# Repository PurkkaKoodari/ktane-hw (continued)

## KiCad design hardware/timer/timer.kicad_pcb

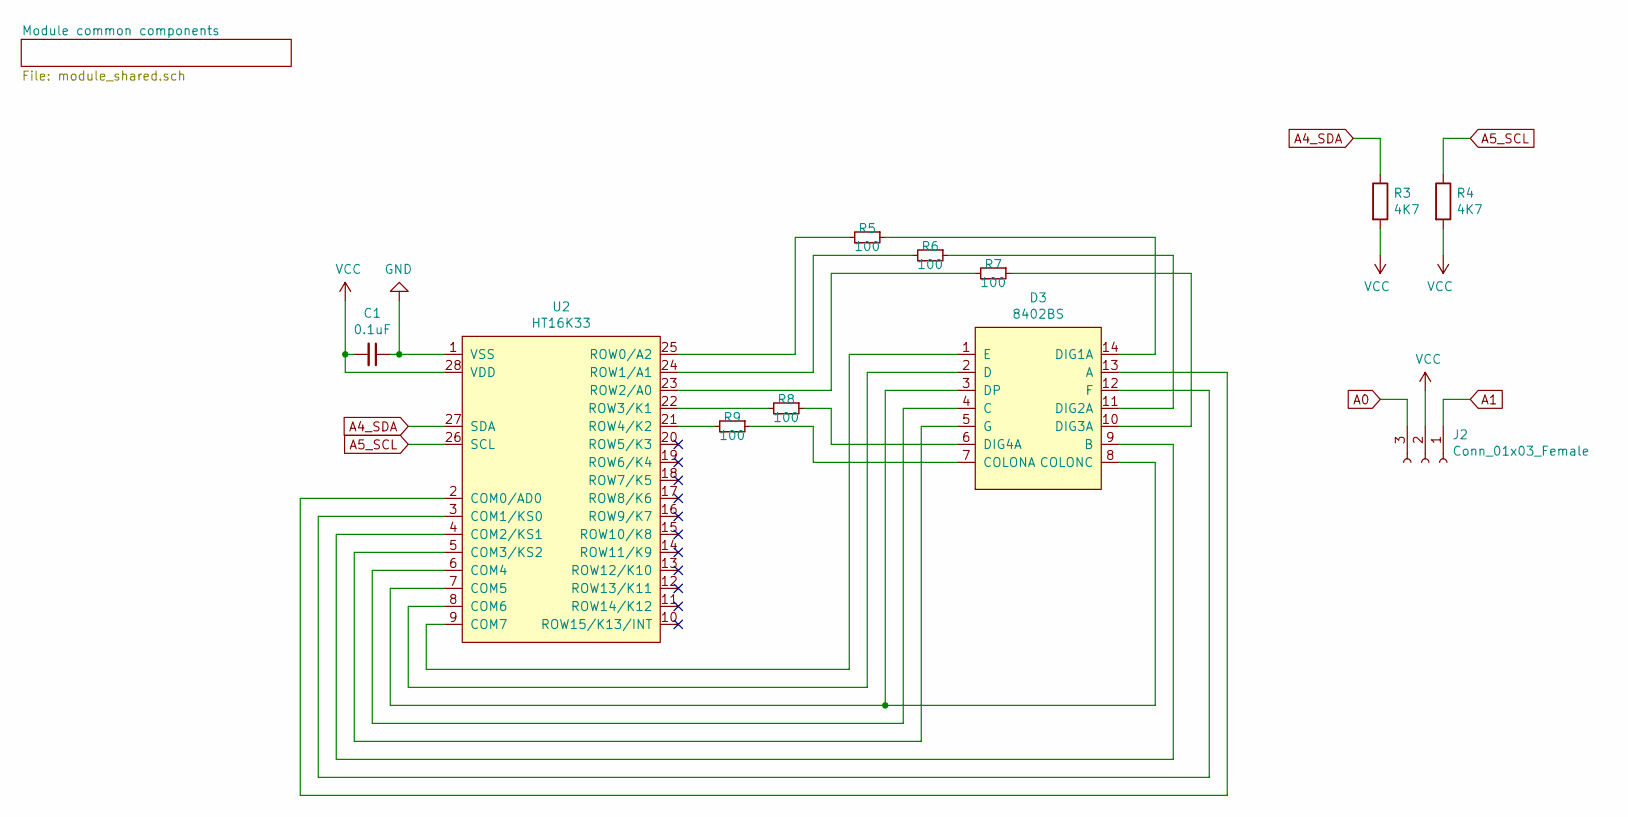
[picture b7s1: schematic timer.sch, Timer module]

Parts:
C1: 0.1uF; C_0603_1608Metric_Pad1.05x0.95mm_HandSolder
D3: 8402BS
J2: Conn_01x03_Female; PinSocket_1x03_P2.54mm_Vertical
R3, R4: 4K7; R_0603_1608Metric_Pad1.05x0.95mm_HandSolder
R5, R6, R7, R8, R9: 100; R_0603_1608Metric_Pad1.05x0.95mm_HandSolder
U2: HT16K33; SOIC-28W_7.5x17.9mm_P1.27mm

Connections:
A0: J2.3; also elsewhere on the board
A1: J2.1; also elsewhere on the board
A4_SDA: R3.1, U2.27 (SDA); also elsewhere on the board
A5_SCL: R4.1, U2.26 (SCL); also elsewhere on the board
GND: C1.1, U2.1 (VSS); also elsewhere on the board
unnamed: D3.1 (E), U2.9 (COM7)
unnamed: D3.2 (D), U2.8 (COM6)
unnamed: D3.3 (DP), D3.8 (COLONC), U2.7 (COM5)
unnamed: D3.4 (C), U2.6 (COM4)
unnamed: D3.5 (G), U2.5 (COM3/KS2)
unnamed: D3.6 (DIG4A), R8.1
unnamed: D3.7 (COLONA), R9.1
unnamed: D3.9 (B), U2.4 (COM2/KS1)
unnamed: D3.10 (DIG3A), R7.1
unnamed: D3.11 (DIG2A), R6.1
unnamed: D3.12 (F), U2.3 (COM1/KS0)
unnamed: D3.13 (A), U2.2 (COM0/AD0)
unnamed: D3.14 (DIG1A), R5.1
unnamed: R5.2, U2.25 (ROW0/A2)
unnamed: R6.2, U2.24 (ROW1/A1)
unnamed: R7.2, U2.23 (ROW2/A0)
unnamed: R8.2, U2.22 (ROW3/K1)
unnamed: R9.2, U2.21 (ROW4/K2)
VCC: C1.2, J2.2, R3.2, R4.2, U2.28 (VDD); also elsewhere on the board

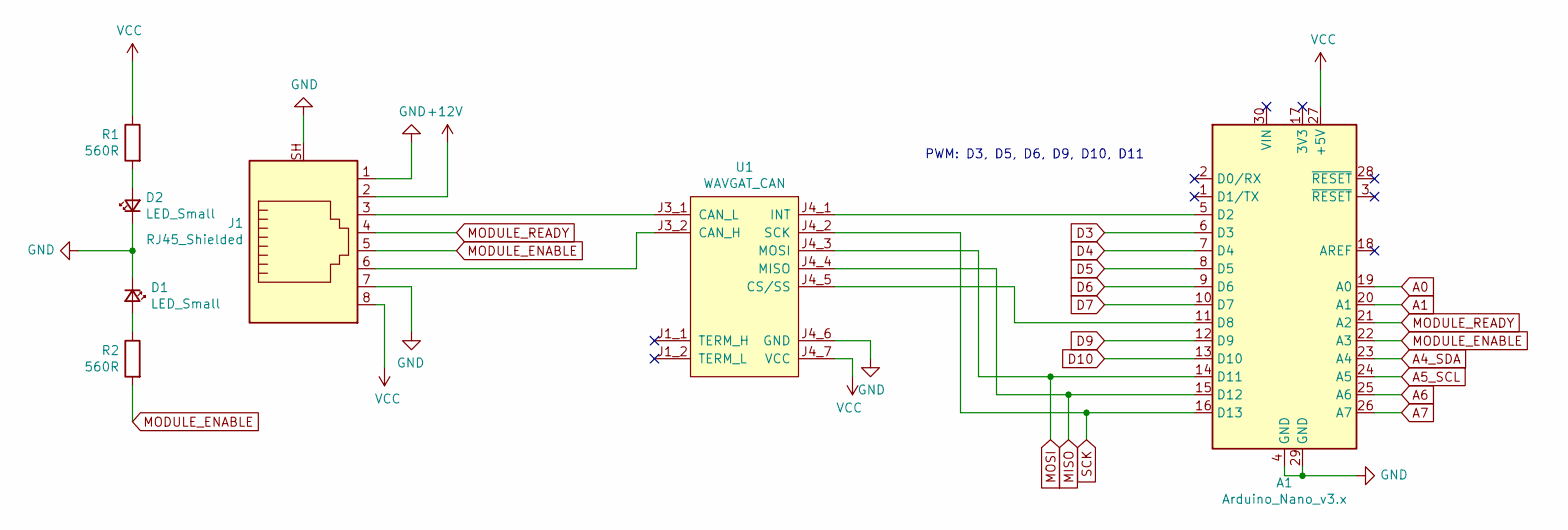
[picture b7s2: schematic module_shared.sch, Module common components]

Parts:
A1: Arduino_Nano_v3.x; Arduino_Nano
D1, D2: LED_Small; LED_D3.0mm
J1: RJ45_Shielded; RJ45_5224
R1, R2: 560R; R_0603_1608Metric_Pad1.05x0.95mm_HandSolder
U1: WAVGAT_CAN

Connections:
+12V: J1.2
A0: A1.19 (A0); also elsewhere on the board
A1: A1.20 (A1); also elsewhere on the board
A4_SDA: A1.23 (A4); also elsewhere on the board
A5_SCL: A1.24 (A5); also elsewhere on the board
A6: A1.25 (A6)
A7: A1.26 (A7)
D3: A1.6 (D3)
D4: A1.7 (D4)
D5: A1.8 (D5)
D6: A1.9 (D6)
D7: A1.10 (D7)
D9: A1.12 (D9)
D10: A1.13 (D10)
GND: A1.4 (GND), A1.29 (GND), D1.1 (K), D2.1 (K), J1.1, J1.7, J1.SH, U1.J4_6 (GND); also elsewhere on the board
MISO: A1.15 (D12), U1.J4_4 (MISO)
MODULE_ENABLE: A1.22 (A3), J1.5, R2.2
MODULE_READY: A1.21 (A2), J1.4
MOSI: A1.14 (D11), U1.J4_3 (MOSI)
unnamed: A1.5 (D2), U1.J4_1 (INT)
unnamed: A1.11 (D8), U1.J4_5 (CS/SS)
unnamed: D1.2 (A), R2.1
unnamed: D2.2 (A), R1.2
unnamed: J1.3, U1.J3_1 (CAN_L)
unnamed: J1.6, U1.J3_2 (CAN_H)
SCK: A1.16 (D13), U1.J4_2 (SCK)
VCC: A1.27 (+5V), J1.8, R1.1, U1.J4_7 (VCC); also elsewhere on the board

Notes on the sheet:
PWM: D3, D5, D6, D9, D10, D11

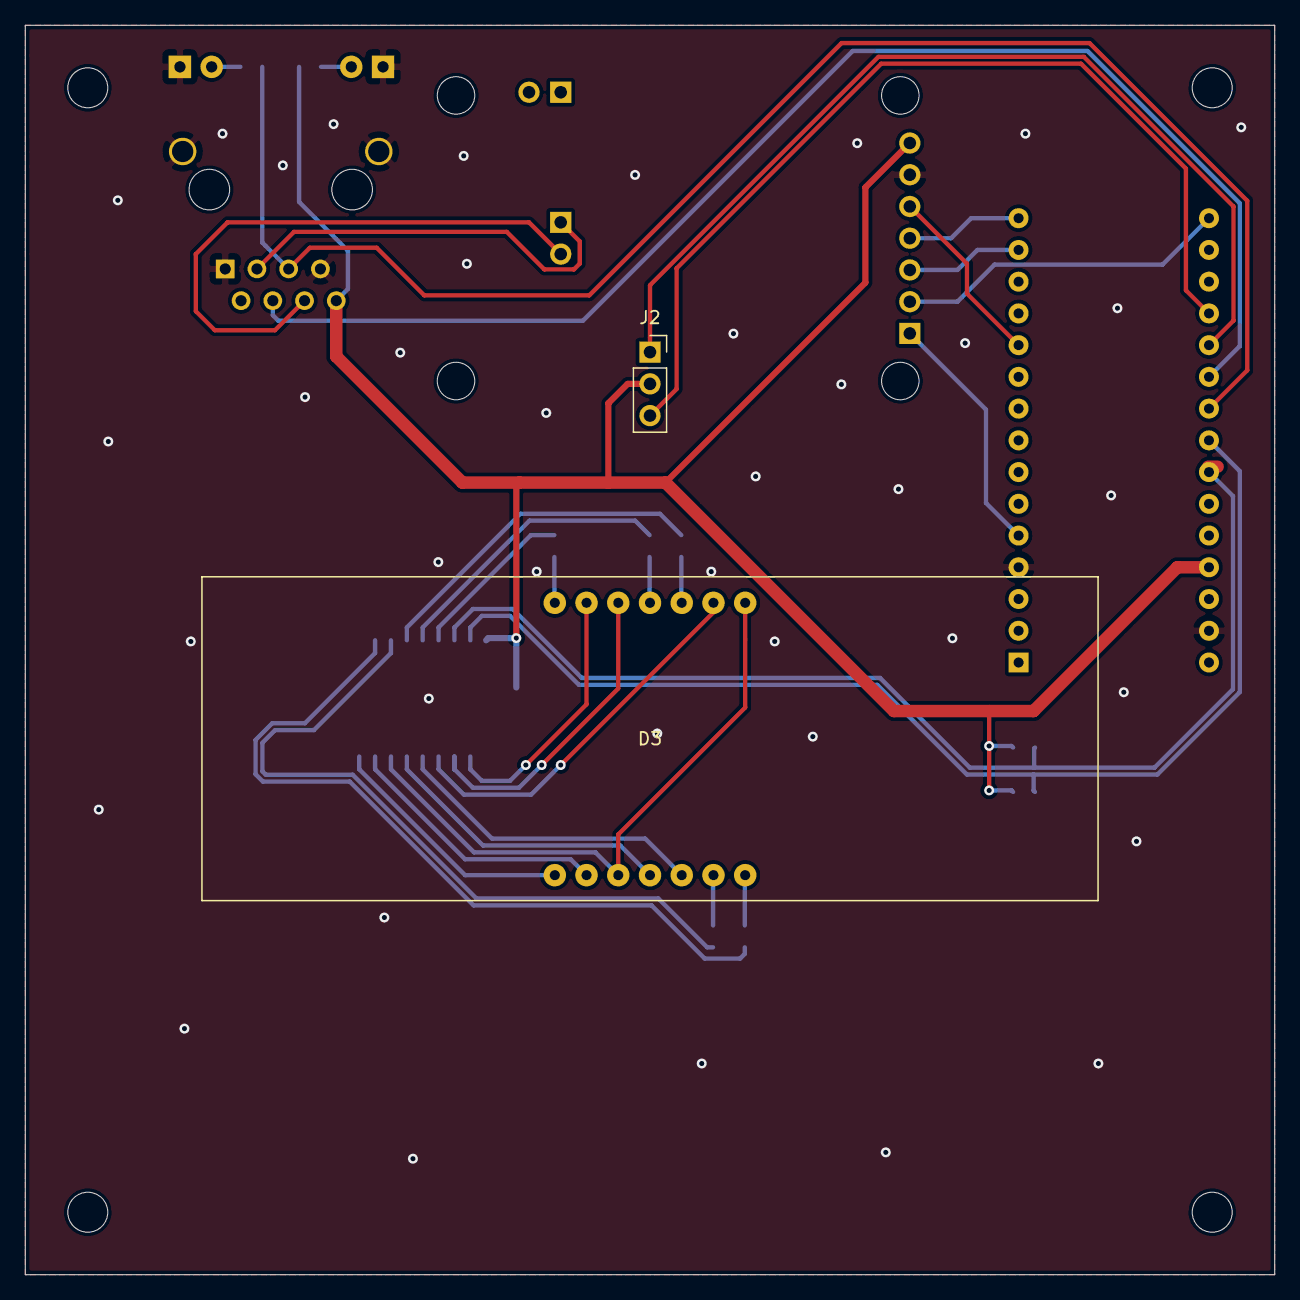
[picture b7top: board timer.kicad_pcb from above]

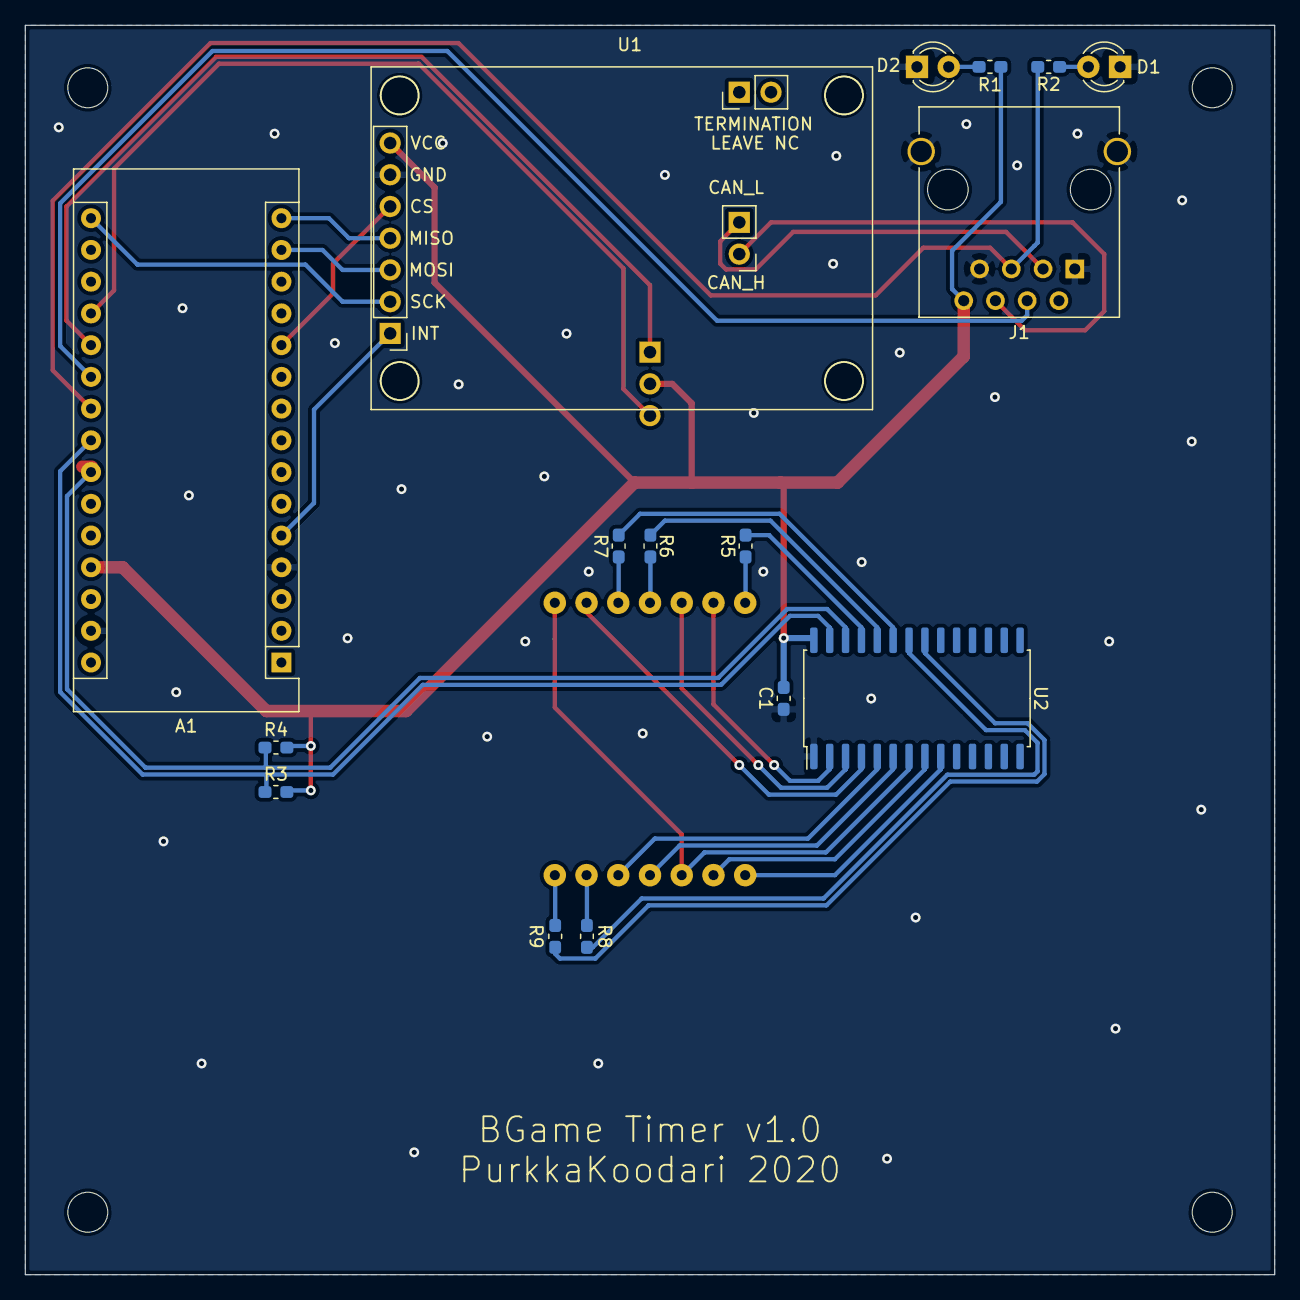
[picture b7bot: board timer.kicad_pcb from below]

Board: 2 copper layers, 100.0 x 100.0 mm, 18 parts (16 on the bottom side), 35 nets.

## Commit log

2019-10-07 Initial project commit.
2019-10-07 Iter 2019-10-07
2019-10-08 Refactor PCB files from root folder -> hardware/
2019-10-10 Start work on bus protocol specification
2019-10-11 Bus protocol spec 1.0-a2: add module states, some messages, error IDs
2019-10-11 Bus protocol spec 1.0-a3: fixes
2019-10-11 Bus protocol spec 1.0-a4: improve spec for Announce message
2019-10-11 Bus protocol spec 1.0-a5: clarify message types section
2019-10-26 Start of main controller: module and bomb classes, message class hierarchy, message parsing, Simon Says as example
2019-10-26 Minor fixes to code style
2019-10-28 Add start of audio system, other minor additions
2019-10-28 Finish backplane release candidate.
2019-10-28 Bus protocol spec 1.0-a6: add delayed initialization as 0x03, move ping to 0x04
2019-10-28 Add root PCB for module design.
2019-10-28 Add initialization sequence, timer module, some refactoring
2019-10-29 Bus protocol spec 1.0-a7: new init sequence, specified physical layer
2019-11-04 Add GPIO code, update to protocol 1.0-a7
2019-11-04 Add interrupt support to GPIO
2019-11-04 Properly implement Wires, Keypad, Simon Says and Timer
2019-11-06 Move everything to using async, add some logging
2019-11-06 Backplane mid term checkup revision.
2019-11-08 Reorient RJ45 connectors in backplane, make interrupt pins accessible in IO Expanders
2019-11-11 Finish first iteration of module common backplane
2019-11-12 Use loop.call_soon instead of custom function
2019-11-12 Add PyCharm files
2019-11-12 Start web UI, rewrite most events, fix Simon solution
2019-11-12 Make event handlers non-reentrant by default
2019-11-18 Add +5V and +12V to module funcitonal PCB.
2019-11-18 Add keepout removig unnecessary small ground plane.
2019-11-20 Add FETs for increased current control.
2019-11-30 Bus protocol spec 1.0-a8: updated MODULE_READY signal, other small changes
2019-11-30 Move MCP23017 to own file, update init sequence to 1.0-a8
2019-12-02 Add bomb defuse/explode logic, change SimonSays messages
2019-12-02 Start of mock hardware implementation for testing
2019-12-02 Add up-to-date GPIO pins and document Casing
2019-12-02 Implement missing messages and crash simulation in Mock
2019-12-02 Add timer adapter pcb
2019-12-05 Add missing awaits to mock code
2019-12-05 Add audio system and Simon sounds
2019-12-06 Fix BombSerial initialization
2019-12-06 Add logging, move configs to config.py, minor fixes
2019-12-06 Add initial version of test shell
2019-12-07 Change PyCharm project to Python 3.8
2019-12-07 Fix debug shell feature
2019-12-07 Change all imports to absolute, fix code style in lots of places
2019-12-07 Add __repr__s to classes, fix some bugs, improve config.py
2019-12-07 Add start of web UI, fix LOTS OF BUGS so it actually works
2019-12-07 Add password module pcb
2019-12-07 Add copper fills
2019-12-08 Fix Keypad generation, add Password
2019-12-08 Remove unused dependency, minor fixes
2019-12-08 Add verbose logging mode
2019-12-09 Fix VanillaCasing capacity
2019-12-09 Fix GPIO crash
2019-12-09 Change to smbus2 as it is available via pip
2019-12-09 Fix brainfart in GPIO
2019-12-09 Reset module enable pins even if init fails
2019-12-09 Unify game initialization, add option to run shell with physical bomb
2019-12-09 Realize that MCP23017 does not invert outputs
2019-12-09 Add a way to start the game
2019-12-09 Reduce noise in log
2019-12-09 Fix bomb initialization if all modules are instantly ready
2019-12-09 Fix bugs with __members__ and add timer speed-up
2019-12-09 Add missing async
2019-12-09 Fix Simon bug
2020-04-25 Working sound, fixed Simon, rewritten Wires, bomb serial in web, better logging, lots of nasty bugfixes
2020-04-25 Prevent unnecessary tick after explosion
2020-04-25 Bus protocol spec 1.0-a9: added sequence number to pings
2020-04-25 Add current version of module Arduino files
2020-04-25 Move SW_VERSION defines into module-specific files
2020-04-25 Fix timer module display calculations
2020-04-29 Fix symbol library paths and remove unnecessary files from Git
2020-04-30 Clean up prototyping/base module, change to current rj45 connector type
2020-04-30 Recreate timer module with single PCB, clean up libraries
2020-05-01 Redo prototyping module layout: CAN module on back, two rows of pins
2020-05-02 Remove strikes after explosion for Wires
2020-05-02 Add slight fade in/out to Simon sounds for less cracks
2020-05-02 Fix audio distortion by making all sounds quieter
2020-05-05 New backplane schematic
2020-05-05 First revision of PCB layout for backplane v2
2020-09-24 Timer PCB: use non-LED RJ45, update layout, reroute
2020-09-25 Create single-board Password PCB
2020-09-25 Password PCB: spread letters apart and reroute
2020-09-25 Password PCB: switch to correct RGB LED symbol
2020-09-25 Add Keypad PCB
2020-09-25 Timer PCB: add copper fills
2020-09-25 Timer PCB: reduce copper fill clearance
2020-09-25 ModuleBase PCB: change RJ45 jack, add mounting holes, reorganize
2020-09-26 Backplane PCB: add audio filter circuit
2020-09-29 Keypad PCB: add debouncing caps
2020-10-06 Backplane PCB: add overvoltage protection, remove some 0Rs, some reorganization
2020-10-06 Backplane PCB: some rerouting to avoid vias in I2C/CAN
2020-10-06 Backplane PCB: remove 3.3V from backplane connector
2020-10-06 Backplane PCB: thermal pads for power FETs, lots of finishing touches
2020-10-08 Clean up symbol libraries, delete outdated files
2020-10-10 Backplane PCB: add section field to components
2020-10-11 Add missing copper fills and edge cuts
2020-10-18 Backplane PCB: clean up power input, widen a trace
2020-10-21 Add temporary (hopefully) HT1632C library
2020-10-28 Timer PCB: fix mounting hole location
2020-10-28 Add identifying silkscreen text, fix missing connections on ModuleBase
2020-11-04 ModuleBase PCB: add lots of mounting holes and some grounds
2020-11-04 Backplane PCB: add THICC power traces, rotate silkscreen text the same way
2020-11-06 Password PCB: change display polarity
2020-11-06 Add polarity indication to LMD07057BAG symbol
2020-11-06 Timer PCB: fix kicad router brain fart
2020-11-07 Add docstrings in Module base class
2020-11-07 Add .gitignore for module firmware folder
2020-11-07 Add HW version checks for module firmware
2020-11-07 Add module creation guide, template module files and firmware build instructions
2020-11-07 Keypad PCB: add holes for PCB-mounted switches
2020-11-19 Correct casing pins
2020-11-19 Add MODULE_READY and new timer board to firmware
2020-12-01 Password PCB: swap ADC-only pin A6 for A5
2020-12-02 ModuleBase PCB: expose Arduino pins + SPI + more GND/5V
2020-12-03 ModuleBase PCB: longer pads for HT1632C footprint
2020-12-05 Avoid using D10 (SPI SS) pin as input
2020-12-05 Update ht1632_bitbang to support 16x24 matrices
2020-12-05 Add Keypad and Password to firmware, improve serial output
2020-12-05 Firmware fixes for Password
2020-12-05 Update pins for Simon Says
2020-12-05 Main controller support for Password
2020-12-05 Update main controller code for Keypad
2020-12-05 Fix Timer strike pin polarity
2020-12-05 Update Button firmware to use WS2812B
2020-12-05 Add proper edgework support
2020-12-05 Minor bugfixes and refactors
2020-12-06 Add build script for firmware
2020-12-06 Rename module_config.h to .example.h
2020-12-06 Update build script
2020-12-06 Rename field in Keypad message
2020-12-06 Add Button support to main controller
2020-12-06 Update Wires support to latest version
2020-12-06 Make enums uint8_t
2020-12-06 Require a parameter for EventSource listener functions
2020-12-06 Separate bomb management from WebUI to BombGameController
2020-12-06 Add missing args to some events
2020-12-06 Add initial DMX support
2020-12-06 Add room server support
2020-12-06 Update gitignore
2020-12-06 Fix Ctrl-C
2020-12-06 Add virtualenv to IDEA
2020-12-06 Fix bugs and separate main methods
2020-12-06 Update Wires & Complicated Wires firmware
2020-12-06 Avoid some gcc warnings
2020-12-06 Bugfixes to main controller
2020-12-06 Correct Wires pin order, add support for red+blue wires, re-send state after reset
2020-12-06 Avoid crash with unknown modules
2020-12-06 Fix Edgework crash
2020-12-06 Send edgework to client
2020-12-07 Add main controller for Complicated Wires, improve messages
2020-12-07 Fix Complicated Wires LEDs
2020-12-07 Add new module names and fix module locations in WebUI
2020-12-07 Improve casing location names
2020-12-07 Fix module initialization race condition
2020-12-07 Show module details on WebUI
2020-12-07 Add web UI button for starting timer
2020-12-07 Fix bugs in Keypad and Wires
2020-12-07 Render edgework in Web UI
2020-12-08 Add note about voltages in adding_modules.md
2020-12-10 Keypad PCB: fix switch positions
2020-12-10 Backplane PCB: I2S audio and complete relayout
2022-02-13 Create new Preact-based web UI
2022-02-13 Fix bugs in main controller
2022-02-14 Add Venting Gas and bugfixes
2022-02-14 Fixes
2022-02-14 Ignore index.js.map
2022-06-06 Ignore duplicate module states in webui
2022-06-06 Fix room server init
2022-06-06 Fix Venting Gas display in webui
2022-06-06 Add README and LICENSE
2022-08-14 Add new backplane and serial number widget
2022-10-07 Add Finnish as option to Venting Gas
2022-10-07 Bugfix Venting Gas, update (Comp)Wires solutions based on state
2022-10-07 Add rudimentary room music system
2022-10-07 Automatically restart music tracks (for game start)
